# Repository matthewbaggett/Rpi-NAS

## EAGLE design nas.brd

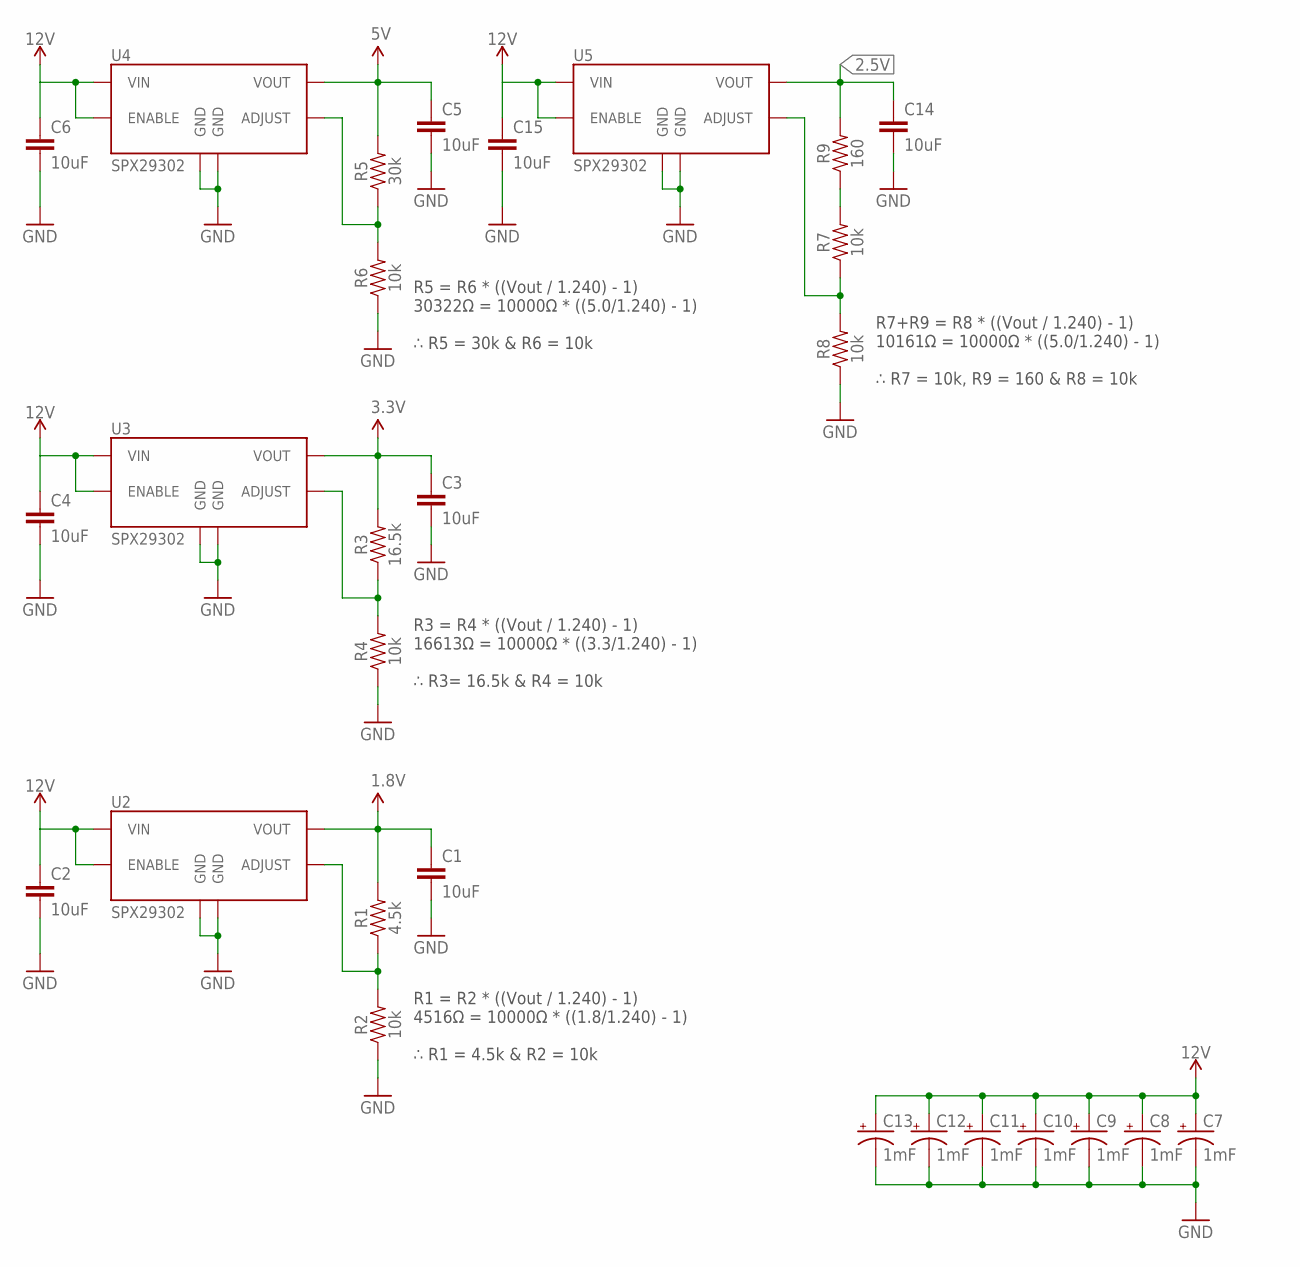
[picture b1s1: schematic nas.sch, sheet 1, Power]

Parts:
C1, C2, C3, C4, C5, C6, C14, C15: 10uF; 1206
C7, C8, C9, C10, C11, C12, C13: 1mF; CPOL-RADIAL-5MM-10MM
R1: 4.5k; 1206
R2, R4, R6, R7, R8: 10k; 1206
R3: 16.5k; 1206
R5: 30k; 1206
R9: 160; 1206
U2, U3, U4, U5: SPX29302; Q5-DD_SPX29300

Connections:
1.8V: C1.1, R1.2, U2.4 (VOUT); also elsewhere on the board
2.5V: C14.1, R9.2, U5.4 (VOUT); also elsewhere on the board
3.3V: C3.1, R3.2, U3.4 (VOUT); also elsewhere on the board
5V: C5.1, R5.2, U4.4 (VOUT); also elsewhere on the board
12V: C2.1, C4.1, C6.1, C7.+, C8.+, C9.+, C10.+, C11.+, C12.+, C13.+, C15.1, U2.1 (ENABLE), U2.2 (VIN), U3.1 (ENABLE), U3.2 (VIN), U4.1 (ENABLE), U4.2 (VIN), U5.1 (ENABLE), U5.2 (VIN); also elsewhere on the board
ADJUST: R1.1, R2.2, U2.5 (ADJUST)
ADJUST1: R3.1, R4.2, U3.5 (ADJUST)
ADJUST2: R5.1, R6.2, U4.5 (ADJUST)
ADJUST3: R7.1, R8.2, U5.5 (ADJUST)
GND: C1.2, C2.2, C3.2, C4.2, C5.2, C6.2, C7.-, C8.-, C9.-, C10.-, C11.-, C12.-, C13.-, C14.2, C15.2, R2.1, R4.1, R6.1, R8.1, U2.3 (GND), U2.6 (GND), U3.3 (GND), U3.6 (GND), U4.3 (GND), U4.6 (GND), U5.3 (GND), U5.6 (GND); also elsewhere on the board
unnamed: R7.2, R9.1

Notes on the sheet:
R1 = R2 * ((Vout / 1.240) - 1) 4516Ω = 10000Ω * ((1.8/1.240) - 1) ∴ R1 = 4.5k & R2 = 10k
R3 = R4 * ((Vout / 1.240) - 1) 16613Ω = 10000Ω * ((3.3/1.240) - 1) ∴ R3= 16.5k & R4 = 10k
R5 = R6 * ((Vout / 1.240) - 1) 30322Ω = 10000Ω * ((5.0/1.240) - 1) ∴ R5 = 30k & R6 = 10k
R7+R9 = R8 * ((Vout / 1.240) - 1) 10161Ω = 10000Ω * ((5.0/1.240) - 1) ∴ R7 = 10k, R9 = 160 & R8 = 10k

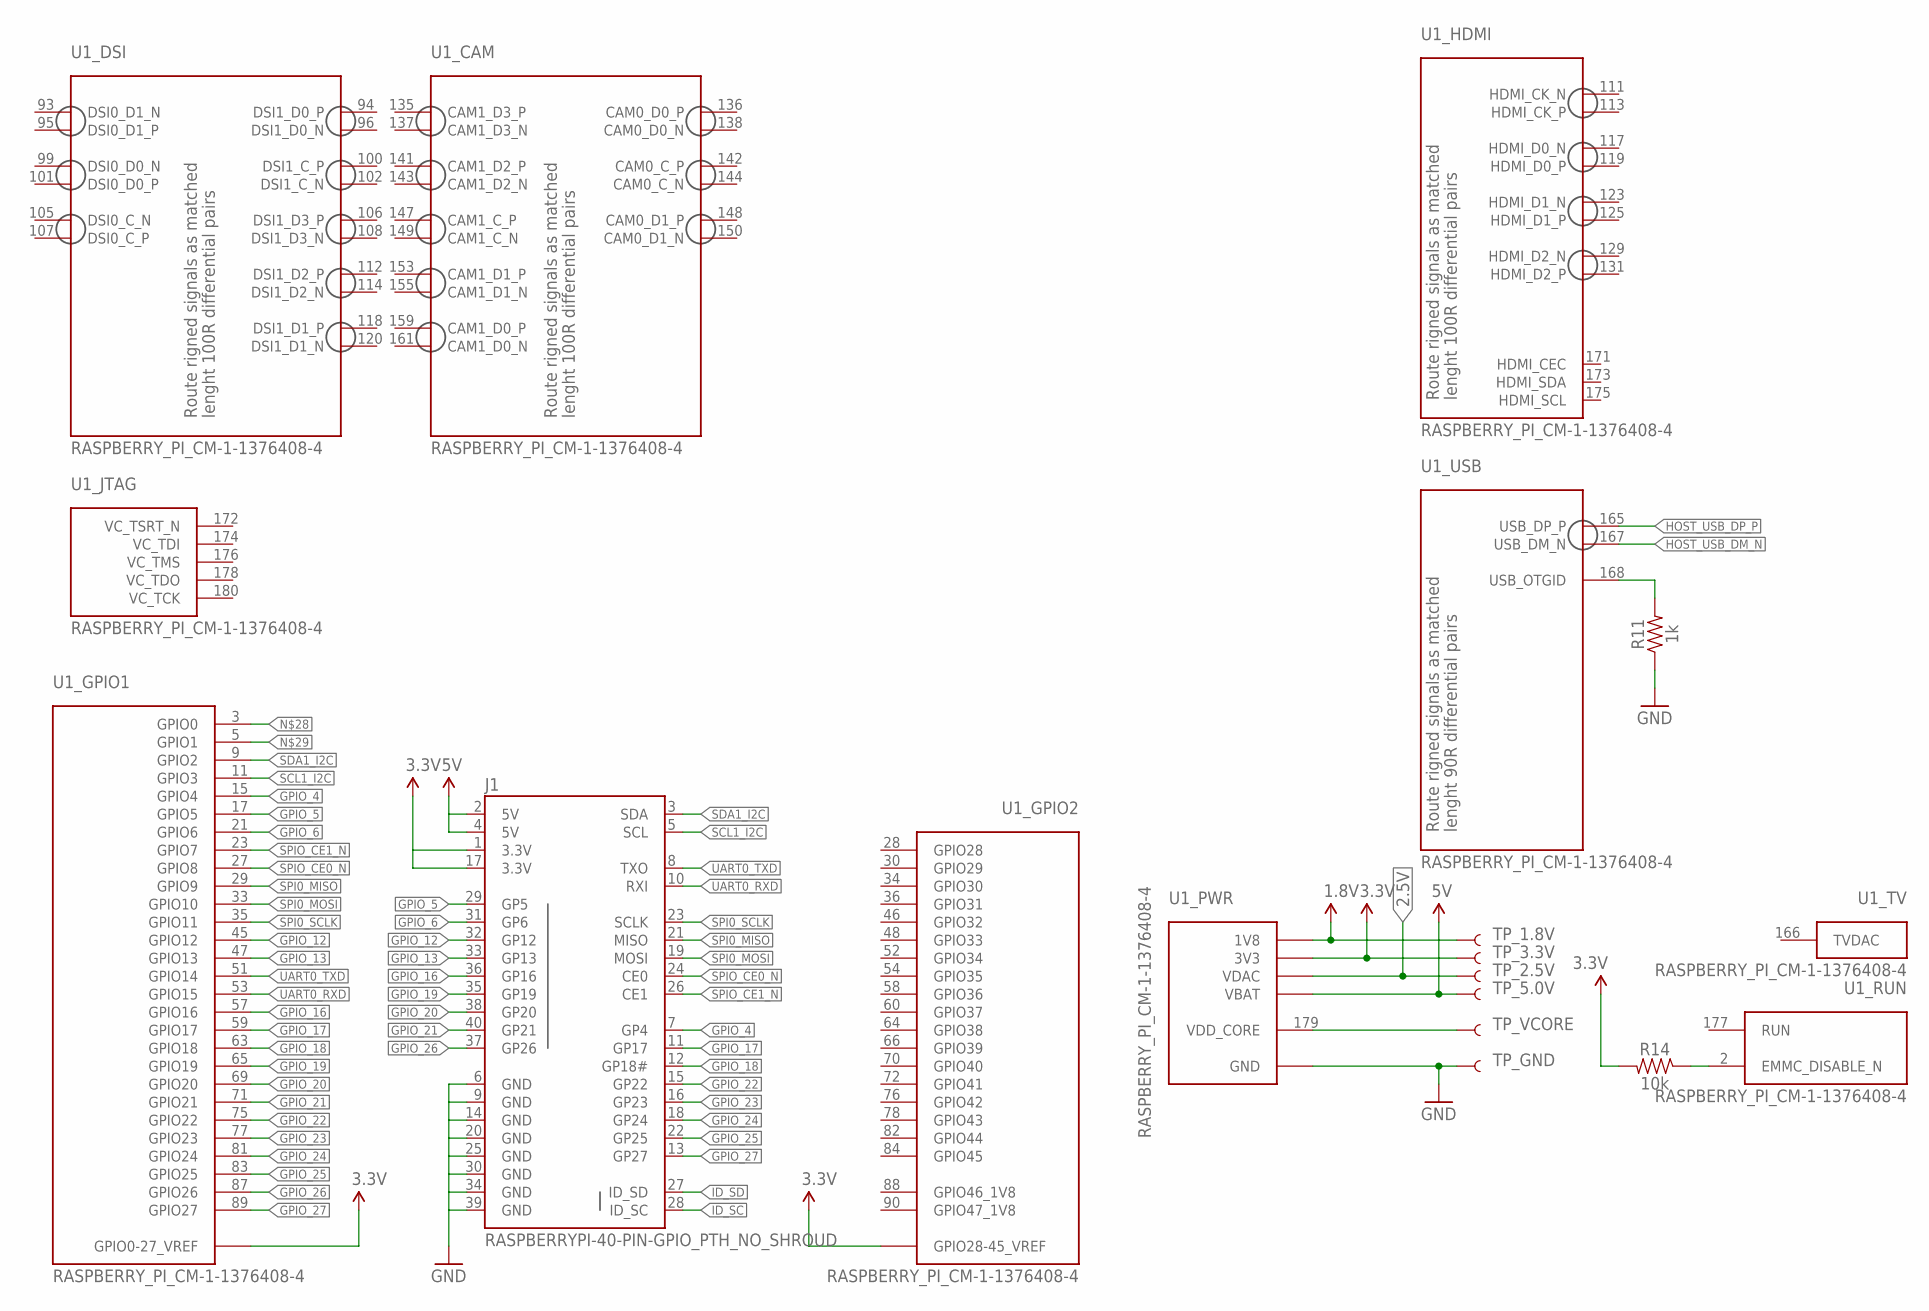
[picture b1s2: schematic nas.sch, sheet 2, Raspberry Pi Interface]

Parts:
J1: RASPBERRYPI-40-PIN-GPIO_PTH_NO_SHROUD; 2X20
R11: 1k; 1206
R14: 10k; 1206
TP_1.8V, TP_2.5V, TP_3.3V, TP_5.0V: TEST-POINT2; PAD.02X.02
TP_GND: TEST-POINT2; PAD.02X.02
TP_VCORE: TEST-POINT2; PAD.02X.02
U1: RASPBERRY_PI_CM-1-1376408-4; 1-1376408-4

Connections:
1.8V: TP_1.8V.P$1, U1.183 (1V8), U1.184 (1V8), U1.185 (1V8), U1.186 (1V8); also elsewhere on the board
2.5V: TP_2.5V.P$1, U1.189 (VDAC), U1.190 (VDAC); also elsewhere on the board
3.3V: J1.1 (3.3V), J1.17 (3.3V), R14.2, TP_3.3V.P$1, U1.39 (GPIO0-27_VREF), U1.40 (GPIO0-27_VREF), U1.41 (GPIO28-45_VREF), U1.42 (GPIO28-45_VREF), U1.191 (3V3), U1.192 (3V3), U1.193 (3V3), U1.194 (3V3); also elsewhere on the board
5V: J1.2 (5V), J1.4 (5V), TP_5.0V.P$1, U1.197 (VBAT), U1.198 (VBAT), U1.199 (VBAT), U1.200 (VBAT); also elsewhere on the board
GND: J1.6 (GND), J1.9 (GND), J1.14 (GND), J1.20 (GND), J1.25 (GND), J1.30 (GND), J1.34 (GND), J1.39 (GND), R11.1, TP_GND.P$1, U1.1 (GND), U1.7 (GND), U1.13 (GND), U1.19 (GND), U1.25 (GND), U1.26 (GND), U1.31 (GND), U1.32 (GND), U1.37 (GND), U1.38 (GND), U1.43 (GND), U1.44 (GND), U1.49 (GND), U1.50 (GND), U1.55 (GND), U1.56 (GND), U1.61 (GND), U1.62 (GND), U1.67 (GND), U1.68 (GND), U1.73 (GND), U1.74 (GND), U1.79 (GND), U1.80 (GND), U1.85 (GND), U1.86 (GND), U1.91 (GND), U1.92 (GND), U1.97 (GND), U1.98 (GND), U1.103 (GND), U1.104 (GND), U1.109 (GND), U1.110 (GND), U1.115 (GND), U1.116 (GND), U1.121 (GND), U1.122 (GND), U1.127 (GND), U1.133 (GND), U1.134 (GND), U1.139 (GND), U1.140 (GND), U1.145 (GND), U1.146 (GND), U1.151 (GND), U1.152 (GND), U1.157 (GND), U1.163 (GND), U1.164 (GND), U1.169 (GND), U1.170 (GND), U1.181 (GND), U1.182 (GND), U1.187 (GND), U1.188 (GND), U1.195 (GND), U1.196 (GND); also elsewhere on the board
GPIO_4: J1.7 (GP4), U1.15 (GPIO4)
GPIO_5: J1.29 (GP5), U1.17 (GPIO5)
GPIO_6: J1.31 (GP6), U1.21 (GPIO6)
GPIO_12: J1.32 (GP12), U1.45 (GPIO12)
GPIO_13: J1.33 (GP13), U1.47 (GPIO13)
GPIO_16: J1.36 (GP16), U1.57 (GPIO16)
GPIO_17: J1.11 (GP17), U1.59 (GPIO17)
GPIO_18: J1.12 (GP18#), U1.63 (GPIO18)
GPIO_19: J1.35 (GP19), U1.65 (GPIO19)
GPIO_20: J1.38 (GP20), U1.69 (GPIO20)
GPIO_21: J1.40 (GP21), U1.71 (GPIO21)
GPIO_22: J1.15 (GP22), U1.75 (GPIO22)
GPIO_23: J1.16 (GP23), U1.77 (GPIO23)
GPIO_24: J1.18 (GP24), U1.81 (GPIO24)
GPIO_25: J1.22 (GP25), U1.83 (GPIO25)
GPIO_26: J1.37 (GP26), U1.87 (GPIO26)
GPIO_27: J1.13 (GP27), U1.89 (GPIO27)
HOST_USB_DM_N: U1.167 (USB_DM_N); also elsewhere on the board
HOST_USB_DP_P: U1.165 (USB_DP_P); also elsewhere on the board
ID_SC: J1.28 (ID_SC)
ID_SD: J1.27 (ID_SD)
unnamed: TP_VCORE.P$1, U1.179 (VDD_CORE)
unnamed: R11.2, U1.168 (USB_OTGID)
unnamed: R14.1, U1.2 (EMMC_DISABLE_N)
SCL1_I2C: J1.5 (SCL), U1.11 (GPIO3)
SDA1_I2C: J1.3 (SDA), U1.9 (GPIO2)
SPI0_MISO: J1.21 (MISO), U1.29 (GPIO9)
SPI0_MOSI: J1.19 (MOSI), U1.33 (GPIO10)
SPI0_SCLK: J1.23 (SCLK), U1.35 (GPIO11)
SPIO_CE0_N: J1.24 (CE0), U1.27 (GPIO8)
SPIO_CE1_N: J1.26 (CE1), U1.23 (GPIO7)
UART0_RXD: J1.10 (RXI), U1.53 (GPIO15)
UART0_TXD: J1.8 (TXO), U1.51 (GPIO14)

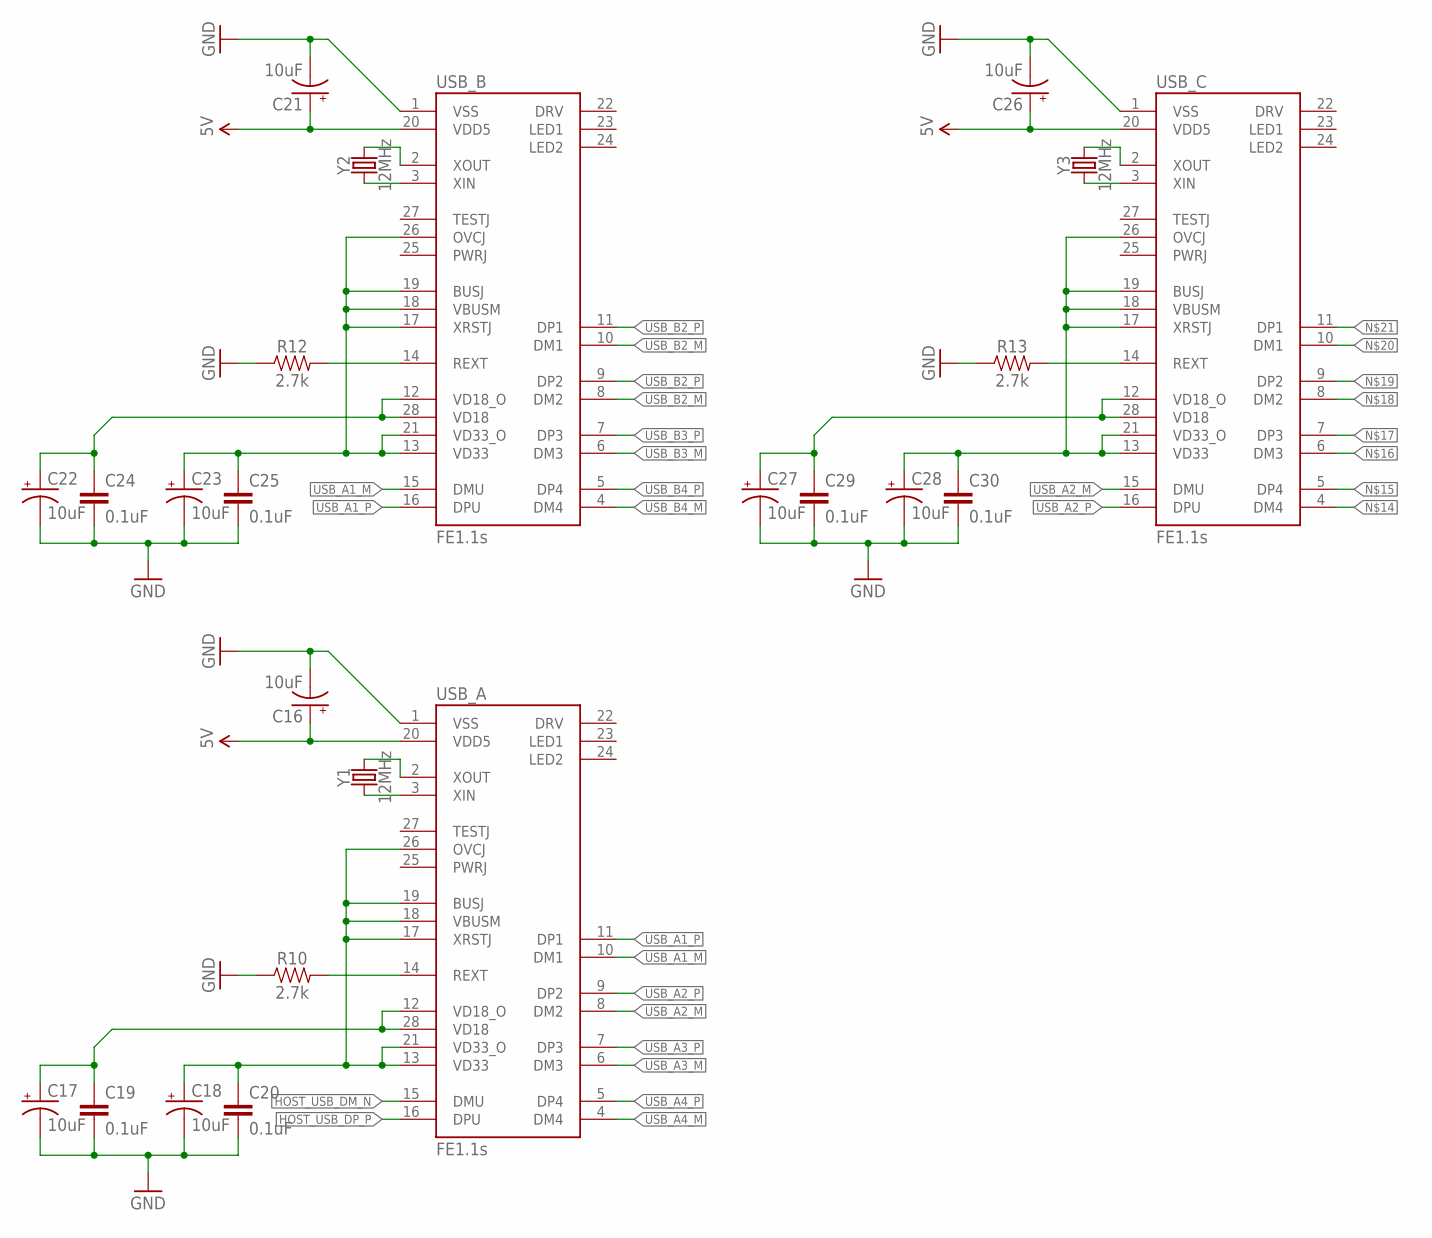
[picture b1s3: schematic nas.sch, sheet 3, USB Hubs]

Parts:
C16, C17, C18, C21, C22, C23, C26, C27, C28: 10uF; EIA3216
C19, C20, C24, C25, C29, C30: 0.1uF; 1206
R10, R12, R13: 2.7k; 1206
USB_A: FE1.1S; FE1.1S_SSOP-28
USB_B: FE1.1S; FE1.1S_SSOP-28
USB_C: FE1.1S; FE1.1S_SSOP-28
Y1, Y2, Y3: 12MHz; CRYSTAL-SMD-5X3.2-4PAD

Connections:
5V: C16.+, C21.+, C26.+, USB_A.20 (VDD5), USB_B.20 (VDD5), USB_C.20 (VDD5); also elsewhere on the board
GND: C16.-, C17.-, C18.-, C19.2, C20.2, C21.-, C22.-, C23.-, C24.2, C25.2, C26.-, C27.-, C28.-, C29.2, C30.2, R10.1, R12.1, R13.1, USB_A.1 (VSS), USB_B.1 (VSS), USB_C.1 (VSS); also elsewhere on the board
HOST_USB_DM_N: USB_A.15 (DMU); also elsewhere on the board
HOST_USB_DP_P: USB_A.16 (DPU); also elsewhere on the board
unnamed: C17.+, C19.1, USB_A.12 (VD18_O), USB_A.28 (VD18)
unnamed: C18.+, C20.1, USB_A.13 (VD33), USB_A.17 (XRSTJ), USB_A.18 (VBUSM), USB_A.19 (BUSJ), USB_A.21 (VD33_O), USB_A.26 (OVCJ)
unnamed: USB_B.3 (XIN), Y2.1
unnamed: USB_A.3 (XIN), Y1.1
unnamed: USB_A.2 (XOUT), Y1.3 (2)
unnamed: USB_B.2 (XOUT), Y2.3 (2)
unnamed: C22.+, C24.1, USB_B.12 (VD18_O), USB_B.28 (VD18)
unnamed: C23.+, C25.1, USB_B.13 (VD33), USB_B.17 (XRSTJ), USB_B.18 (VBUSM), USB_B.19 (BUSJ), USB_B.21 (VD33_O), USB_B.26 (OVCJ)
unnamed: R10.2, USB_A.14 (REXT)
unnamed: R12.2, USB_B.14 (REXT)
unnamed: USB_C.3 (XIN), Y3.1
unnamed: USB_C.2 (XOUT), Y3.3 (2)
unnamed: C27.+, C29.1, USB_C.12 (VD18_O), USB_C.28 (VD18)
unnamed: C28.+, C30.1, USB_C.13 (VD33), USB_C.17 (XRSTJ), USB_C.18 (VBUSM), USB_C.19 (BUSJ), USB_C.21 (VD33_O), USB_C.26 (OVCJ)
unnamed: R13.2, USB_C.14 (REXT)
USB_A1_M: USB_A.10 (DM1), USB_B.15 (DMU)
USB_A1_P: USB_A.11 (DP1), USB_B.16 (DPU)
USB_A2_M: USB_A.8 (DM2), USB_C.15 (DMU)
USB_A2_P: USB_A.9 (DP2), USB_C.16 (DPU)
USB_A3_M: USB_A.6 (DM3)
USB_A3_P: USB_A.7 (DP3)
USB_A4_M: USB_A.4 (DM4)
USB_A4_P: USB_A.5 (DP4)
USB_B2_M: USB_B.8 (DM2), USB_B.10 (DM1); also elsewhere on the board
USB_B2_P: USB_B.9 (DP2), USB_B.11 (DP1); also elsewhere on the board
USB_B3_M: USB_B.6 (DM3)
USB_B3_P: USB_B.7 (DP3)
USB_B4_M: USB_B.4 (DM4)
USB_B4_P: USB_B.5 (DP4)

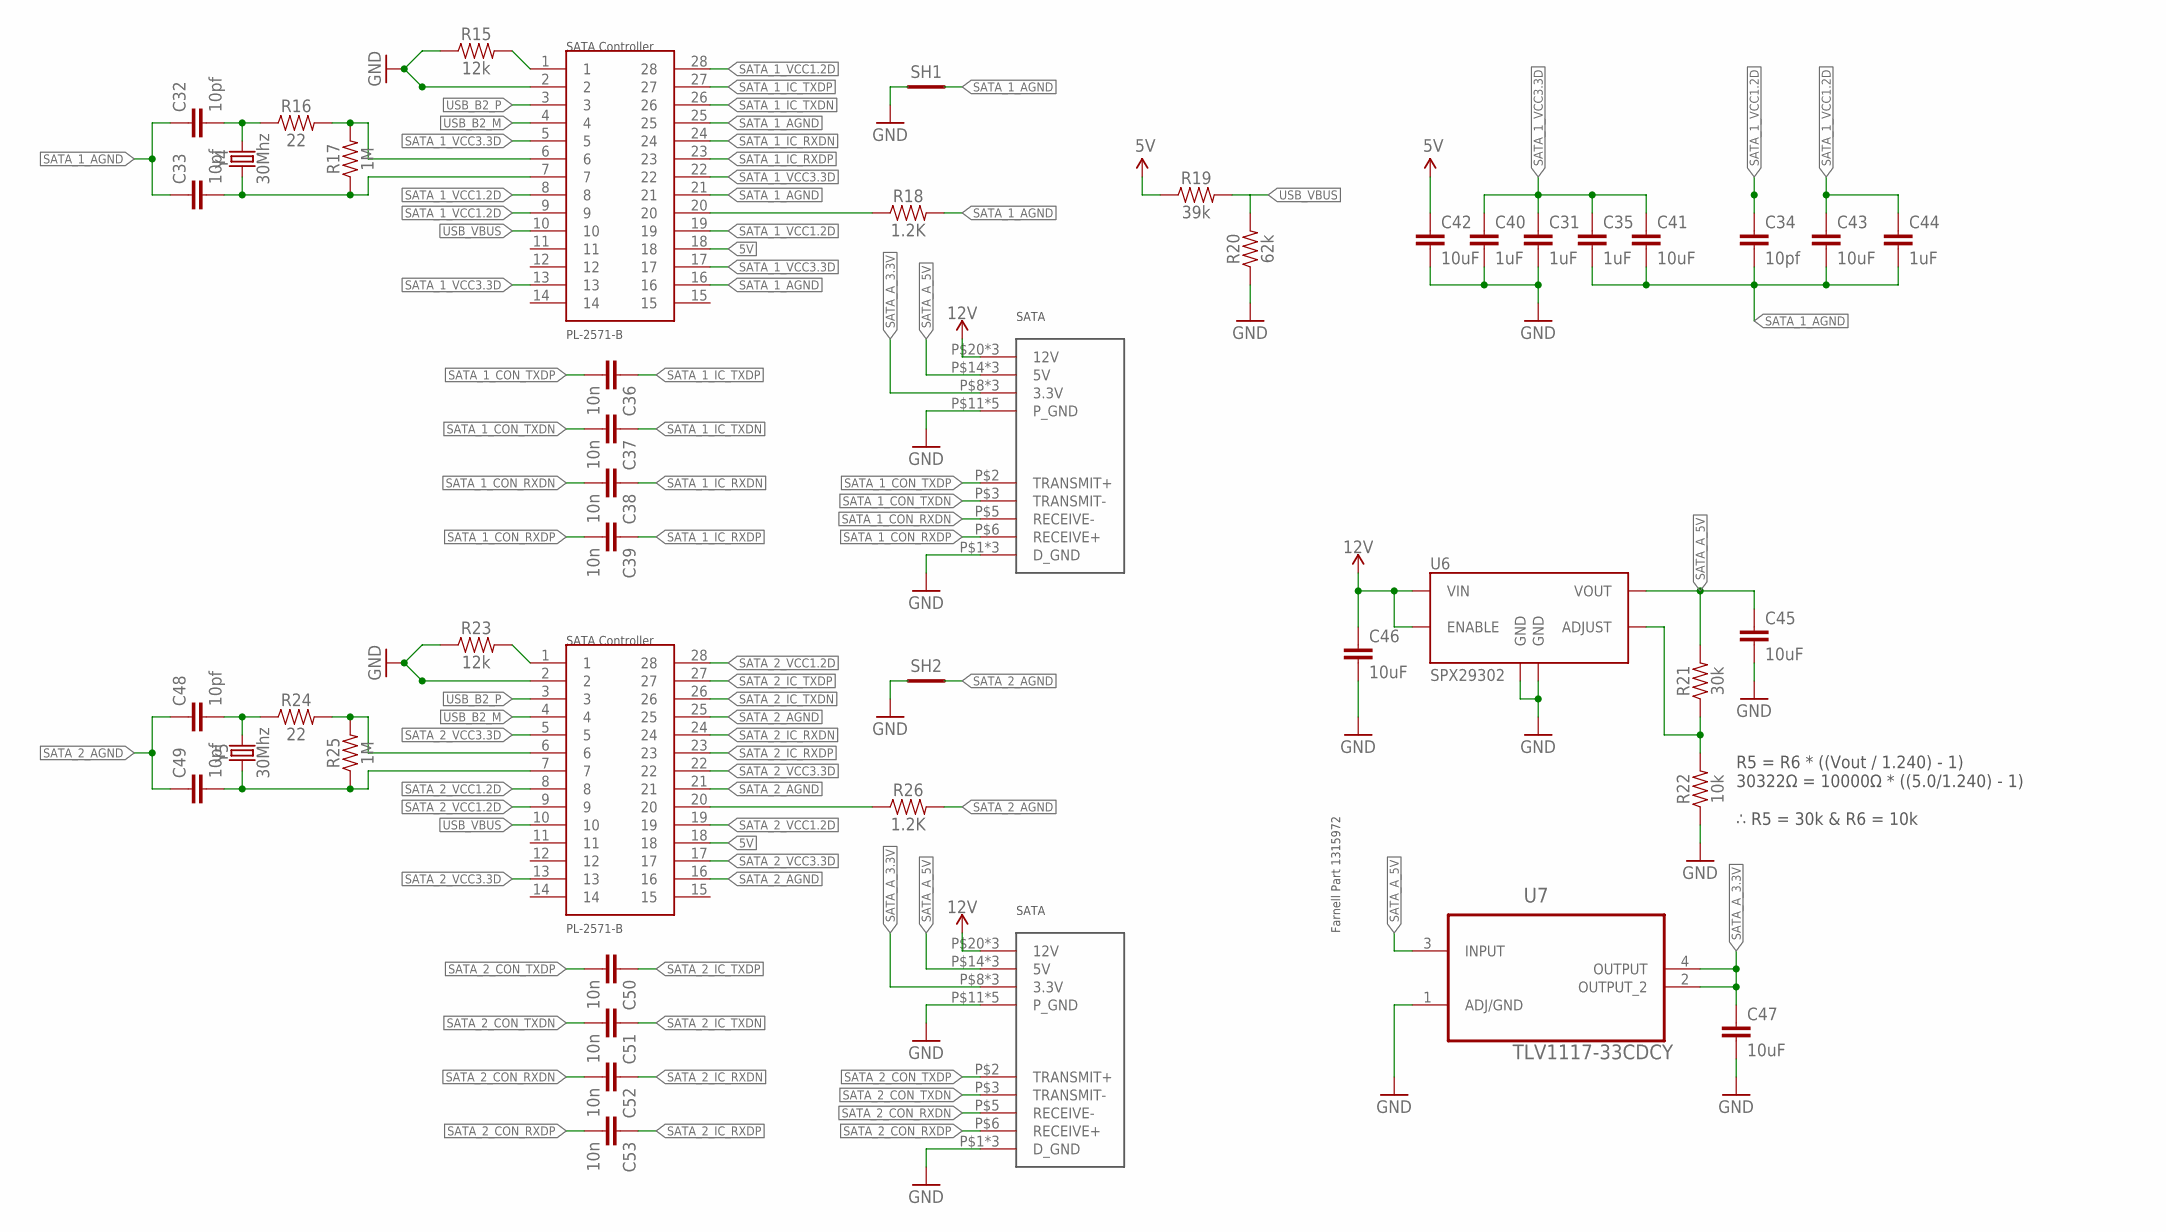
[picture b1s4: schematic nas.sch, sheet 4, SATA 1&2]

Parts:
C31, C35, C40, C44: 1uF; 1206
C32, C33, C34, C48, C49: 10pf; 1206
C36, C37, C38, C39, C50, C51, C52, C53: 10n; 1206
C41, C42, C43, C45, C46, C47: 10uF; 1206
R15, R23: 12k; 1206
R16, R24: 22; 1206
R17, R25: 1M; 1206
R18, R26: 1.2K; 1206
R19: 39k; 1206
R20: 62k; 1206
R21: 30k; 1206
R22: 10k; 1206
SH1, SH2: SHORT-HT5; SHORT_TOP-50
U6: SPX29302; Q5-DD_SPX29300
U7: TLV1117-33CDCY; SOT230P700X180-4N
U$12, U$16: PL-2571-B; SSOP28DB
U$15, U$17: SATA_POWER_AND_DATA; 3M-SATA-5622-1200-ML
Y4, Y5: 30Mhz; CRYSTAL-SMD-5X3.2-4PAD

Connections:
5V: C42.1, R19.1, U$12.18, U$16.18; also elsewhere on the board
12V: C46.1, U6.1 (ENABLE), U6.2 (VIN), U$15.P$20 (12V), U$15.P$21 (12V), U$15.P$22 (12V), U$17.P$20 (12V), U$17.P$21 (12V), U$17.P$22 (12V); also elsewhere on the board
ADJUST4: R21.1, R22.2, U6.5 (ADJUST)
GND: C31.2, C40.2, C42.2, C45.2, C46.2, C47.2, R15.1, R20.1, R22.1, R23.1, SH1.1, SH2.1, U6.3 (GND), U6.6 (GND), U7.1 (ADJ/GND), U$12.2, U$15.P$1 (D_GND), U$15.P$4 (D_GND), U$15.P$7 (D_GND), U$15.P$11 (P_GND), U$15.P$12 (P_GND), U$15.P$13 (P_GND), U$15.P$17 (P_GND), U$15.P$19 (P_GND), U$16.2, U$17.P$1 (D_GND), U$17.P$4 (D_GND), U$17.P$7 (D_GND), U$17.P$11 (P_GND), U$17.P$12 (P_GND), U$17.P$13 (P_GND), U$17.P$17 (P_GND), U$17.P$19 (P_GND); also elsewhere on the board
unnamed: R23.2, U$16.1
unnamed: R15.2, U$12.1
unnamed: R18.1, U$12.20
unnamed: C49.2, R25.1, U$16.7, Y5.1
unnamed: R24.2, R25.2, U$16.6
unnamed: C48.2, R24.1, Y5.3 (2)
unnamed: R26.1, U$16.20
unnamed: C33.2, R17.1, U$12.7, Y4.1
unnamed: R16.2, R17.2, U$12.6
unnamed: C32.2, R16.1, Y4.3 (2)
SATA_1_AGND: C32.1, C33.1, C34.2, C35.2, C41.2, C43.2, C44.2, R18.2, SH1.2, U$12.16, U$12.21, U$12.25
SATA_1_CON_RXDN: C38.2, U$15.P$5 (RECEIVE-)
SATA_1_CON_RXDP: C39.2, U$15.P$6 (RECEIVE+)
SATA_1_CON_TXDN: C37.2, U$15.P$3 (TRANSMIT-)
SATA_1_CON_TXDP: C36.2, U$15.P$2 (TRANSMIT+)
SATA_1_IC_RXDN: C38.1, U$12.24
SATA_1_IC_RXDP: C39.1, U$12.23
SATA_1_IC_TXDN: C37.1, U$12.26
SATA_1_IC_TXDP: C36.1, U$12.27
SATA_1_VCC1.2D: C34.1, C43.1, C44.1, U$12.8, U$12.9, U$12.19, U$12.28
SATA_1_VCC3.3D: C31.1, C35.1, C40.1, C41.1, U$12.5, U$12.13, U$12.17, U$12.22
SATA_2_AGND: C48.1, C49.1, R26.2, SH2.2, U$16.16, U$16.21, U$16.25
SATA_2_CON_RXDN: C52.2, U$17.P$5 (RECEIVE-)
SATA_2_CON_RXDP: C53.2, U$17.P$6 (RECEIVE+)
SATA_2_CON_TXDN: C51.2, U$17.P$3 (TRANSMIT-)
SATA_2_CON_TXDP: C50.2, U$17.P$2 (TRANSMIT+)
SATA_2_IC_RXDN: C52.1, U$16.24
SATA_2_IC_RXDP: C53.1, U$16.23
SATA_2_IC_TXDN: C51.1, U$16.26
SATA_2_IC_TXDP: C50.1, U$16.27
SATA_2_VCC1.2D: U$16.8, U$16.9, U$16.19, U$16.28
SATA_2_VCC3.3D: U$16.5, U$16.13, U$16.17, U$16.22
SATA_A_3.3V: C47.1, U7.2 (OUTPUT_2), U7.4 (OUTPUT), U$15.P$8 (3.3V), U$15.P$9 (3.3V), U$15.P$10 (3.3V), U$17.P$8 (3.3V), U$17.P$9 (3.3V), U$17.P$10 (3.3V)
SATA_A_5V: C45.1, R21.2, U6.4 (VOUT), U7.3 (INPUT), U$15.P$14 (5V), U$15.P$15 (5V), U$15.P$16 (5V), U$17.P$14 (5V), U$17.P$15 (5V), U$17.P$16 (5V)
USB_B2_M: U$12.4, U$16.4; also elsewhere on the board
USB_B2_P: U$12.3, U$16.3; also elsewhere on the board
USB_VBUS: R19.2, R20.2, U$12.10, U$16.10

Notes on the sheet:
SATA Controller
PL-2571-B
R5 = R6 * ((Vout / 1.240) - 1) 30322Ω = 10000Ω * ((5.0/1.240) - 1) ∴ R5 = 30k & R6 = 10k
Farnell Part 1315972

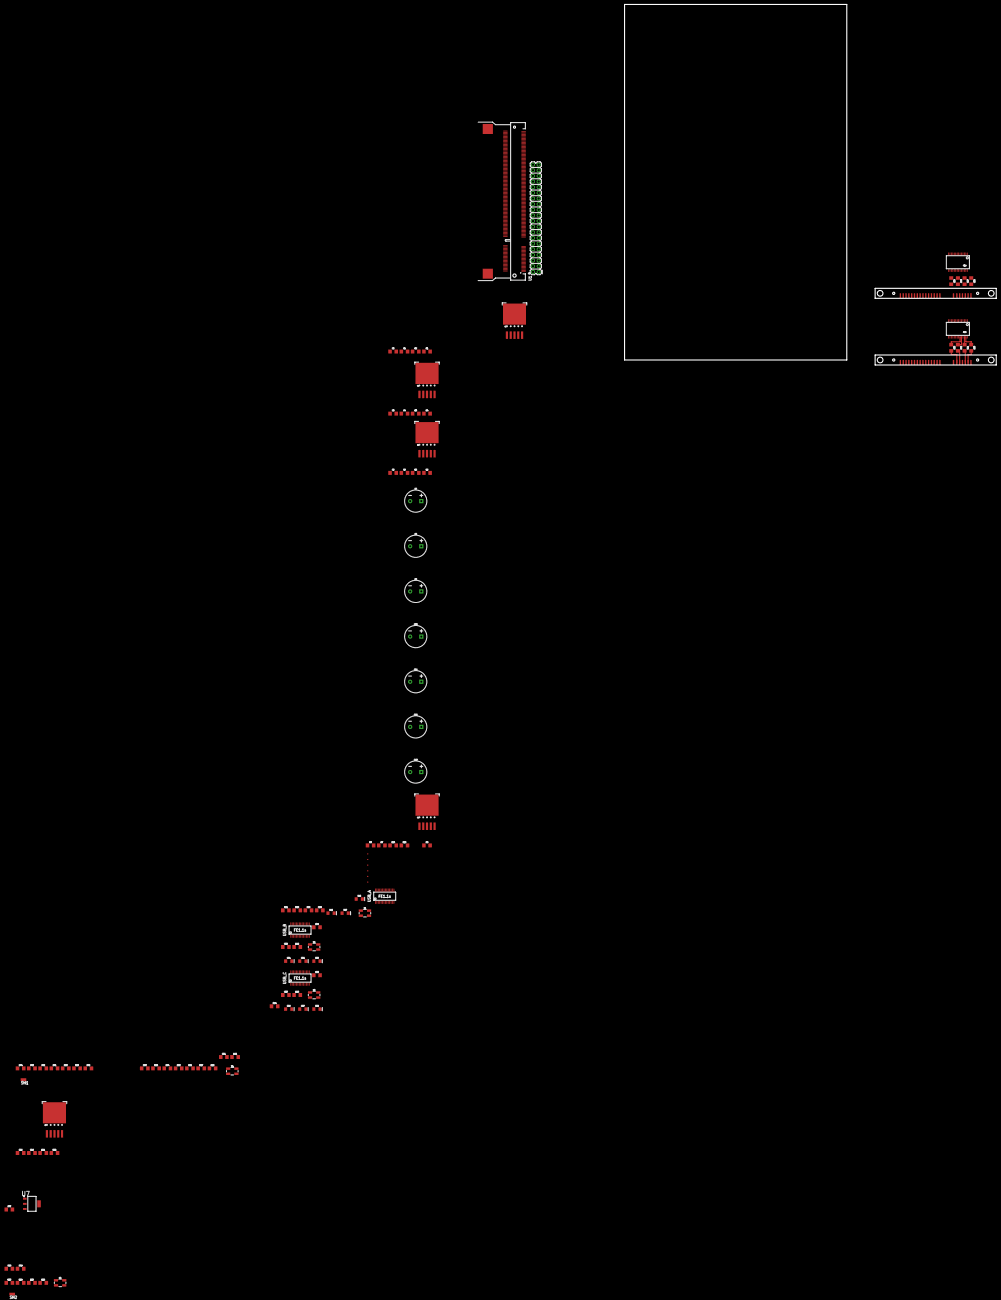
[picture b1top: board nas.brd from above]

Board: 2 copper layers, 167.2 x 162.2 mm, 107 parts (0 on the bottom side), 99 nets.

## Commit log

2017-08-19 Initial
2017-08-19 Breaking up into many pages

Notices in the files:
parts and their libraries:
SparkFun-IC-Power: Licensing: Creative Commons ShareAlike 4.0 International - https://creativecommons.org/licenses/by-sa/4.0
SparkFun: Licensing: CC v3.0 Share-Alike You are welcome to use this library for commercial purposes.
